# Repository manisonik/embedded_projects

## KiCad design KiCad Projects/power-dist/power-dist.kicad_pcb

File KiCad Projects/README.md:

# embedded_projects
Safe source for KiCad , LTspice, and MicroCap projects.

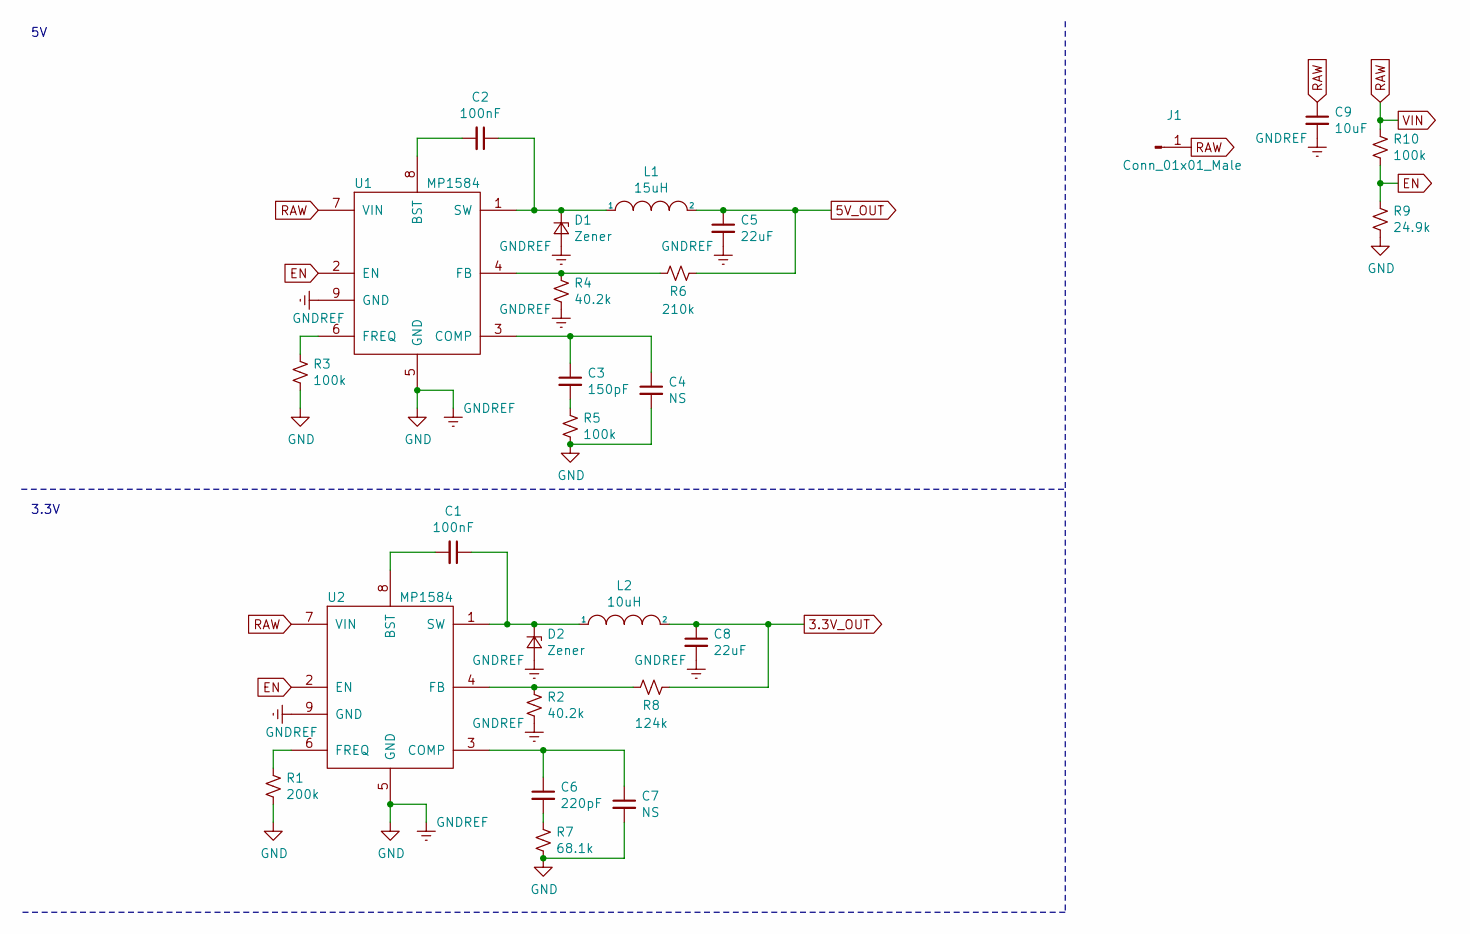
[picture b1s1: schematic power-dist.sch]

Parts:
C1, C2: 100nF; C_0201
C3: 150pF; C_0201
C4, C7: NS; C_0201
C5, C8: 22uF; C_0201
C6: 220pF; C_0201
C9: 10uF; CP_Elec_4x4.5
D1, D2: Zener; D_0603
J1: Conn_01x01_Male; SolderWirePad_4xSquare_0-8mmDrill
L1: 15uH; L_1210
L2: 10uH; L_1210
R1: 200k; R_0201
R2, R4: 40.2k; R_0201
R3, R5, R10: 100k; R_0201
R6: 210k; R_0201
R7: 68.1k; R_0201
R8: 124k; R_0201
R9: 24.9k; R_0201
U1, U2: MP1584; SOIC-8-1EP_3.9x4.9mm_Pitch1.27mm

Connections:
3.3V_OUT: C8.1, L2.2, R8.1
5V_OUT: C5.1, L1.2, R6.1
EN: R9.1, R10.2, U1.2 (EN), U2.2 (EN)
GND: C4.2, C5.2, C7.2, C8.2, C9.2, D1.2 (A), D2.2 (A), R1.2, R2.2, R3.2, R4.2, R5.2, R7.2, R9.2, U1.5 (GND), U1.9 (GND), U2.5 (GND), U2.9 (GND)
unnamed: C1.1, D2.1 (K), L2.1, U2.1 (SW)
unnamed: C1.2, U2.8 (BST)
unnamed: C2.1, D1.1 (K), L1.1, U1.1 (SW)
unnamed: C2.2, U1.8 (BST)
unnamed: C3.1, C4.1, U1.3 (COMP)
unnamed: C3.2, R5.1
unnamed: C6.1, C7.1, U2.3 (COMP)
unnamed: C6.2, R7.1
unnamed: R1.1, U2.6 (FREQ)
unnamed: R2.1, R8.2, U2.4 (FB)
unnamed: R3.1, U1.6 (FREQ)
unnamed: R4.1, R6.2, U1.4 (FB)
RAW: C9.1, J1.1, R10.1, U1.7 (VIN), U2.7 (VIN)

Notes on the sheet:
3.3V

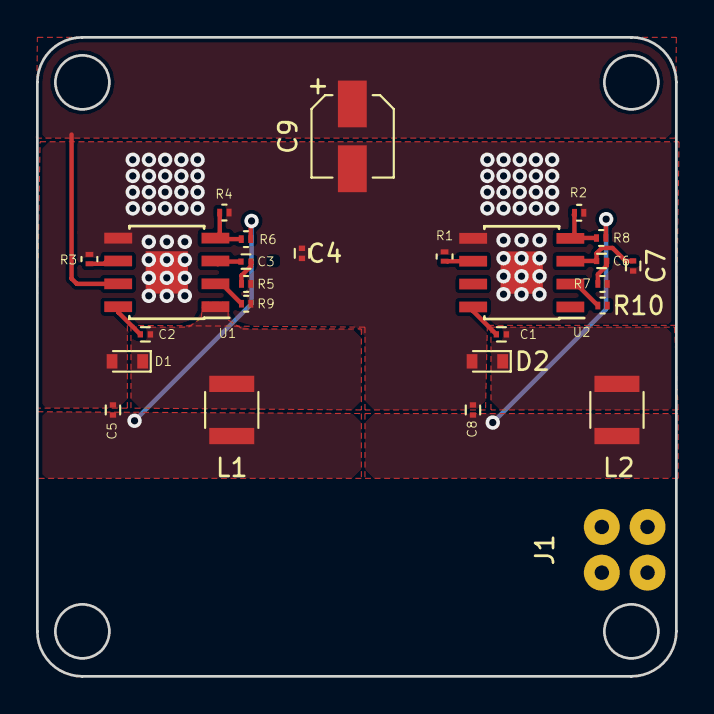
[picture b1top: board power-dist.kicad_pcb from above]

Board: 2 copper layers, 35.5 x 35.5 mm, 26 parts (0 on the bottom side), 17 nets.

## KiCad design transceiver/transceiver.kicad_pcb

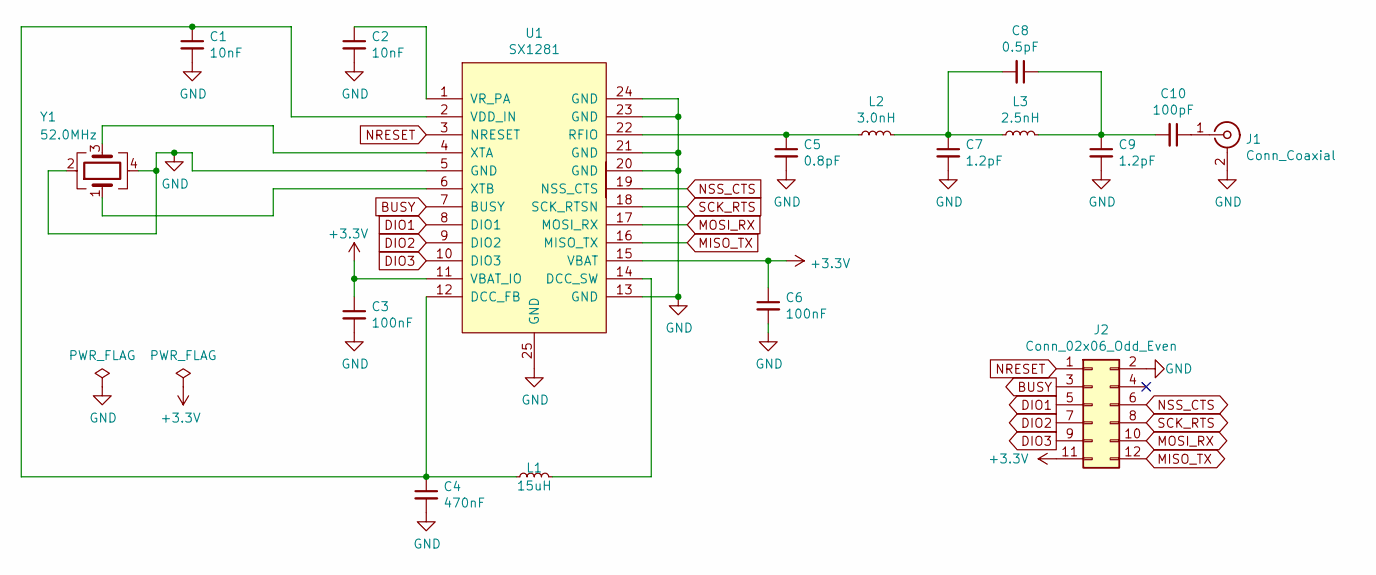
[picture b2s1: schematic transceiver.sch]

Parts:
C1, C2: 10nF; C_0402
C3, C6: 100nF; C_0402
C4: 470nF; C_0402
C5: 0.8pF; C_0402
C7, C9: 1.2pF; C_0402
C8: 0.5pF; C_0402
C10: 100pF; C_0402
J1: Conn_Coaxial; SMA_Amphenol_132289_EdgeMount
J2: Conn_02x06_Odd_Even; Molex_C-Grid_III_90130-1112_2x12_P2.54mm_Vertical
L1: 15uH; L_0805
L2: 3.0nH; L_0402
L3: 2.5nH; L_0402
U1: SX1281; QFN-24-1EP_4x4mm_Pitch0.5mm
Y1: 52.0MHz; Crystal_SMD_2016-4pin_2.0x1.6mm

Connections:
+3V3: C3.1, C6.1, J2.11, U1.11 (VBAT_IO), U1.15 (VBAT)
BUSY: J2.3, U1.7 (BUSY)
DIO1: J2.5, U1.8 (DIO1)
DIO2: J2.7, U1.9 (DIO2)
DIO3: J2.9, U1.10 (DIO3)
GND: C1.2, C2.2, C3.2, C4.2, C5.2, C6.2, C7.2, C9.2, J1.2 (Ext), J2.2, U1.5 (GND), U1.13 (GND), U1.20 (GND), U1.21 (GND), U1.23 (GND), U1.24 (GND), U1.25 (GND), Y1.2, Y1.4
MISO_TX: J2.12, U1.16 (MISO_TX)
MOSI_RX: J2.10, U1.17 (MOSI_RX)
NRESET: J2.1, U1.3 (NRESET)
NSS_CTS: J2.6, U1.19 (NSS_CTS)
unnamed: C1.1, C4.1, L1.1, U1.2 (VDD_IN), U1.12 (DCC_FB)
unnamed: C2.1, U1.1 (VR_PA)
unnamed: C5.1, L2.1, U1.22 (RFIO)
unnamed: C7.1, C8.2, L2.2, L3.1
unnamed: C10.1, J1.1 (In)
unnamed: C8.1, C9.1, C10.2, L3.2
unnamed: L1.2, U1.14 (DCC_SW)
unnamed: U1.4 (XTA), Y1.3
unnamed: U1.6 (XTB), Y1.1
SCK_RTS: J2.8, U1.18 (SCK_RTSN)

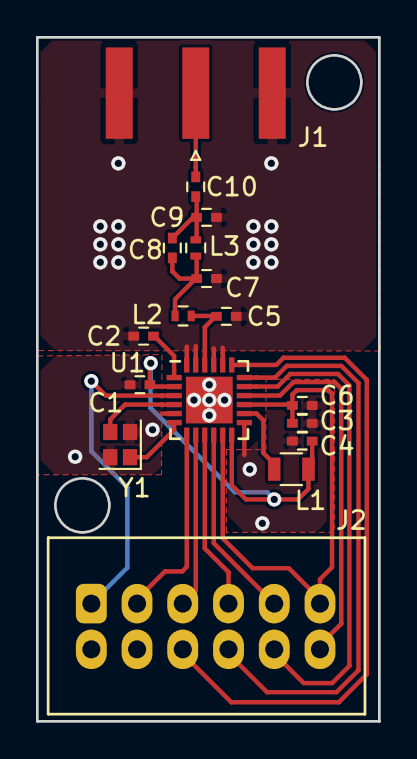
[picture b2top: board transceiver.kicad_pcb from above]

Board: 2 copper layers, 19.0 x 38.0 mm, 17 parts (0 on the bottom side), 20 nets.

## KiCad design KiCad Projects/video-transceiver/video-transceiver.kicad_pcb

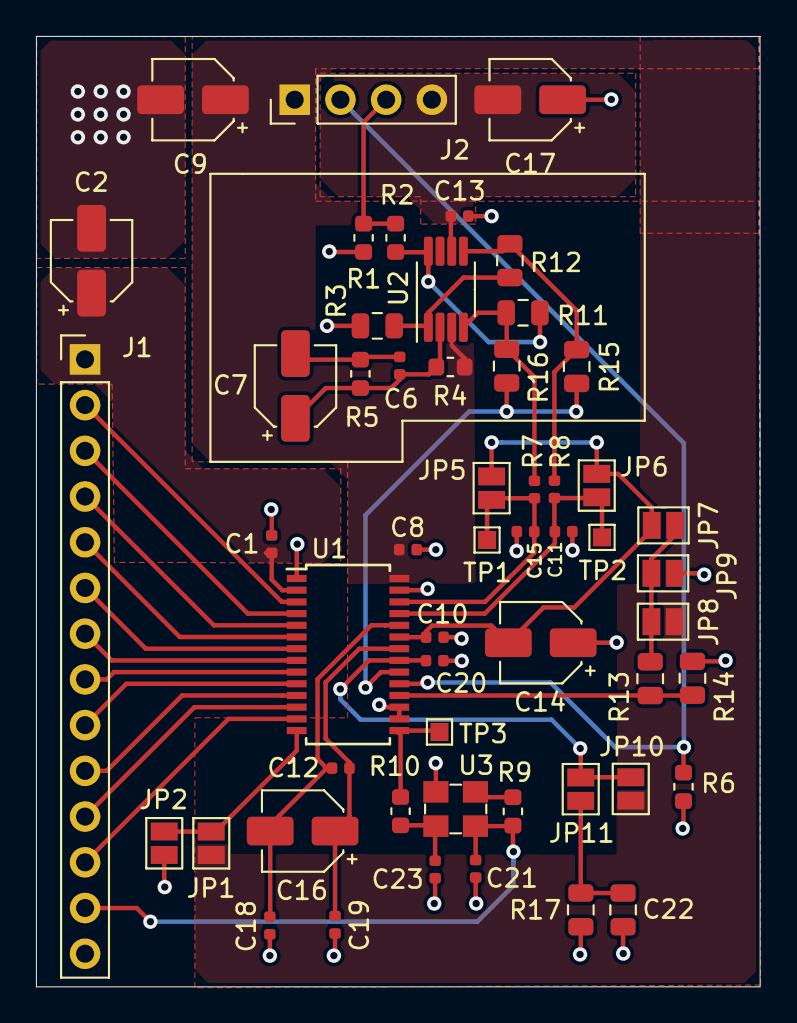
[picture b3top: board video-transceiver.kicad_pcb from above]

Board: 2 copper layers, 40.2 x 52.8 mm, 54 parts (0 on the bottom side), 38 nets.

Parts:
C1, C6, C8, C10, C12, C13, C18, C19, C20, C21: 0.1uF; C_0402_1005Metric
C2, C7, C9, C14, C16, C17: 10uF; CP_Elec_4x5.4
C11, C15: 20pF; C_0402_1005Metric
C22: 1uF; C_0805_2012Metric
C23: 15pF; C_0402_1005Metric
J1: Conn_01x14_Male; PinHeader_1x14_P2.54mm_Vertical
J2: Conn_01x04_Male; PinHeader_1x04_P2.54mm_Vertical
JP1, JP2, JP5, JP6, JP7, JP8, JP9, JP10, JP11: Jumper; SolderJumper-2_P1.3mm_Open_Pad1.0x1.5mm
R1, R6, R10: 50R; R_0603_1608Metric
R2: 1R; R_0603_1608Metric
R3: 25R; R_0805_2012Metric
R4, R5, R9: 1k; R_0603_1608Metric
R7, R8: 10R; R_0402_1005Metric
R11, R12, R13, R14, R15, R16, R17: TBD; R_0805_2012Metric
TP1, TP2, TP3: TestPoint; TestPoint_Pad_1.0x1.0mm
U1: AD9203; TSSOP-28_4.4x9.7mm_P0.65mm
U2: AD8138; MSOP-8_3x3mm_P0.65mm
U3: SIT8208AI-2F-33E-27.000000Y; Oscillator_SMD_SiT8208-4Pin_3.2x2.5mm_P0.75mm

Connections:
A: R8.1, R12.1, R15.2, U2.5
AVDD: C8.2, C9.1, J2.1, JP1.2, JP8.1, JP10.2, R4.2, U1.28, U2.3
AVSS: C13.1, C17.2, J2.4, U2.6
B: R7.1, R11.1, R16.2, U2.4
CLAMP: J2.2, R6.2, U1.19
CLK: R10.1, TP3.1, U1.15
D0: J1.2, U1.3
D1: J1.3, U1.4
D2: J1.4, U1.5
D3: J1.5, U1.6
D4: J1.6, U1.7
D5: J1.7, U1.8
D6: J1.8, U1.9
D7: J1.9, U1.10
D8: J1.10, U1.11
D9: J1.11, U1.12
DRVDD: C1.2, C2.1, J1.1, U1.2
GND: C1.1, C2.2, C8.1, C9.2, C10.2, C11.1, C13.2, C14.1, C15.1, C17.1, C18.1, C19.1, C20.1, C21.2, C22.2, C23.2, J1.14, JP2.2, JP9.1, R1.1, R3.2, R6.1, R14.1, R17.2, U1.1, U1.16, U1.17, U1.27, U3.2
unnamed: C6.1, C7.1, R4.1, R5.2, U2.2
unnamed: C6.2, C7.2, R5.1
unnamed: C10.1, C14.2, JP5.2, JP6.2, JP7.2, U1.23
unnamed: C11.2, JP6.1, R8.2, TP2.1, U1.25
unnamed: C12.1, C16.2, C18.2, U1.24
unnamed: C12.2, C16.1, C19.2, U1.22
unnamed: C15.2, JP5.1, R7.2, TP1.1, U1.26
unnamed: C22.1, JP11.2, R17.1
unnamed: C23.1, R10.2, U3.3
unnamed: JP1.1, JP2.1, U1.14
unnamed: JP7.1, JP8.2, JP9.2, R13.2
unnamed: R9.1, U3.1
unnamed: R2.1, R11.2, U2.8
unnamed: R3.1, R12.2, U2.1
unnamed: R15.1, R16.1, U1.20
OTR: J1.12, U1.13
PWRCON: C20.2, JP10.1, JP11.1, U1.21
REFSENSE: R13.1, R14.2, U1.18
VDD: C21.1, J1.13, R9.2, U3.4
VID: J2.3, R1.2, R2.2

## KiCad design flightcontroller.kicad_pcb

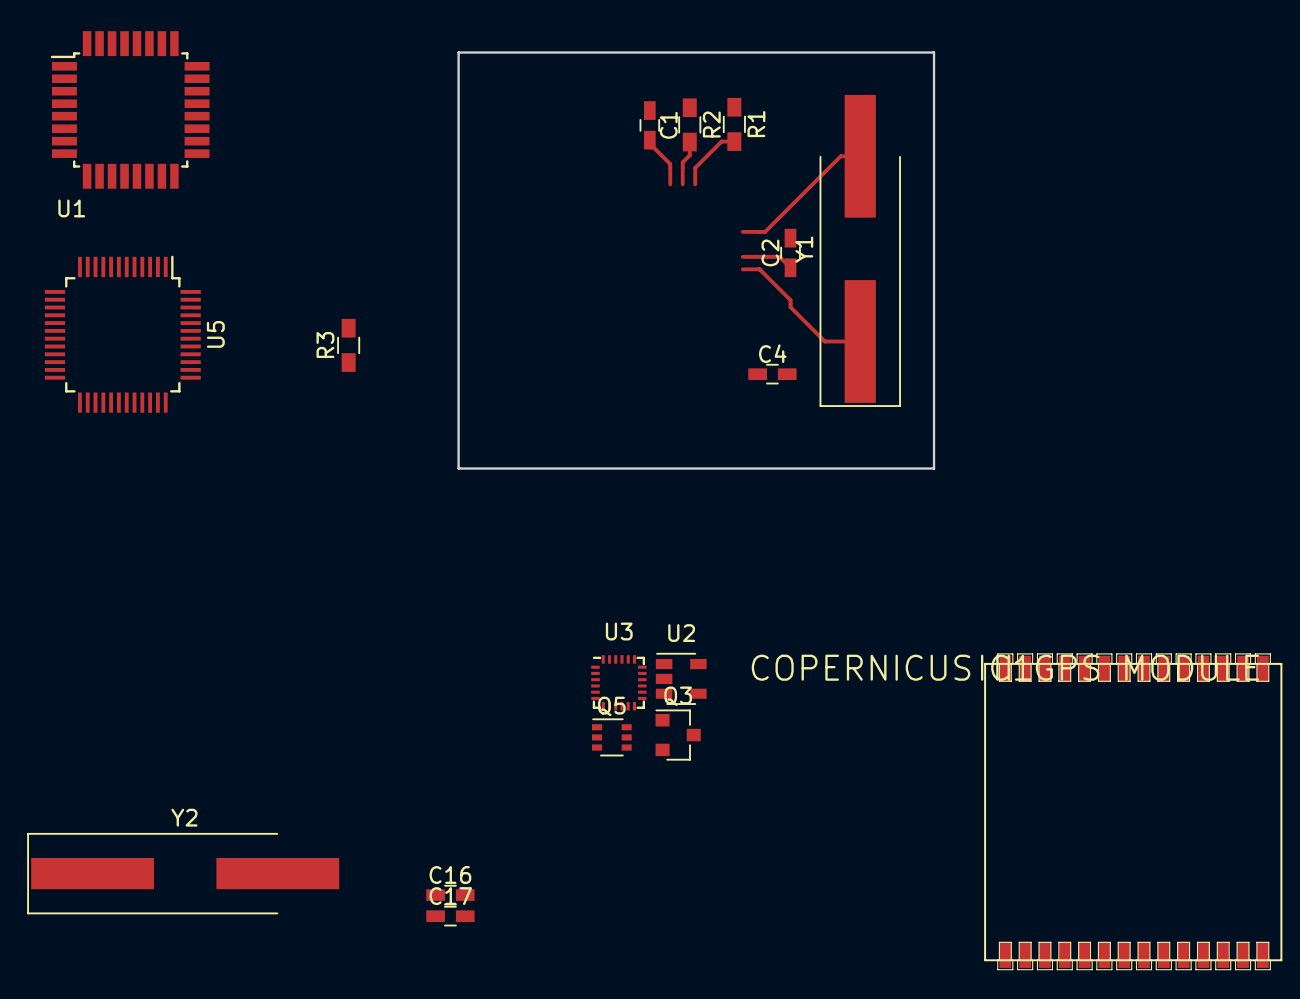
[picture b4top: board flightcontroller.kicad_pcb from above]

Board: 2 copper layers, 30.5 x 26.7 mm, 17 parts (0 on the bottom side), 15 nets.

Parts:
C1, C4: 0.1uF; C_0603_HandSoldering
C2: 10uF; C_0603_HandSoldering
C16, C17: 10pF; C_0603_HandSoldering
IC1: COPERNICUS II GPS MODULE; COPERNICUS
Q3: CMPT404A; SOT-23
Q5: FDG6316P; SOT-363_SC-70-6
R1: 1k; R_0603_HandSoldering
R2: 100k; R_0603_HandSoldering
R3: 10K; R_0603_HandSoldering
U1: BMP180; TQFP-32_7x7mm_Pitch0.8mm
U2: MIC5219-3.3BM5; SOT-23-5
U3: MPU-9250; QFN-24_3x3mm_Pitch0.4mm
U5: STM32F103CBTx; LQFP-48_7x7mm_Pitch0.5mm
Y1: 8; Crystal_SMD_HC49-SD_HandSoldering
Y2: 8MHz; Crystal_SMD_HC49-SD_HandSoldering

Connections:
GND: C1.2, C2.2, C4.2, C16.2, C17.2, IC1.1, IC1.2, IC1.4, IC1.13, IC1.14, IC1.15, IC1.27, IC1.28, R3.2, U1.7, U2.2, U3.18, U5.8, U5.23, U5.35, U5.47
unnamed: C4.1, U3.10
unnamed: U5.5, Y1.1
unnamed: U5.6, Y1.2
unnamed: Q3.1, R1.1
unnamed: IC1.5, Q5.2, R2.2
unnamed: Q3.2, Q5.1
OSCA: C16.1, Y2.1
OSCB: C17.1, Y2.2
RAW: C2.1, U2.1, U2.3
RXDB: IC1.20, U5.31
SCL: U3.23, U5.42
SDA: U1.6, U3.24, U5.43
TXDA: IC1.23, U5.30
VCC: C1.1, IC1.6, IC1.12, Q5.3, R2.1, U1.2, U1.3, U2.5, U3.8, U3.13, U5.9, U5.24, U5.36, U5.48

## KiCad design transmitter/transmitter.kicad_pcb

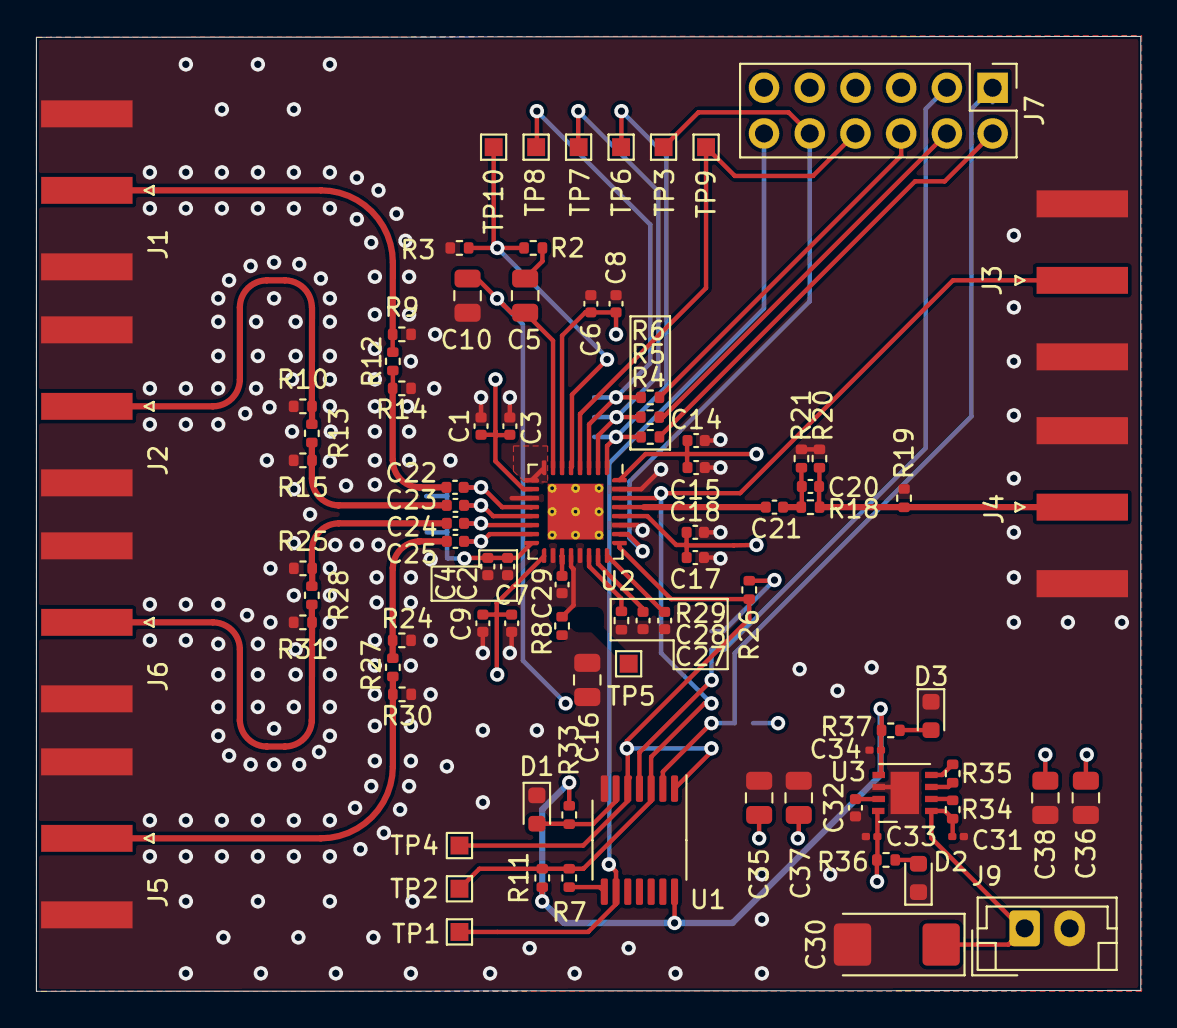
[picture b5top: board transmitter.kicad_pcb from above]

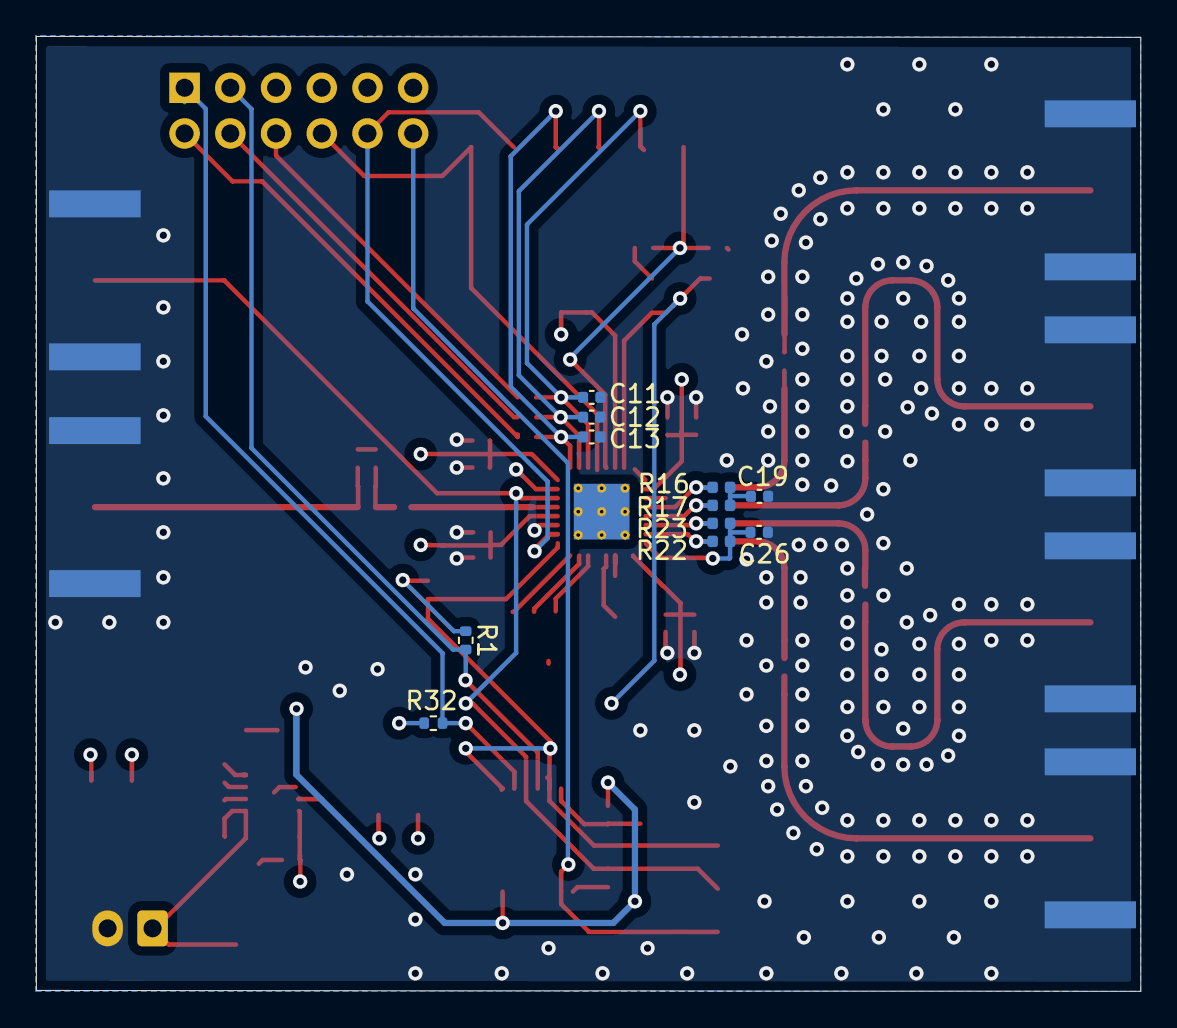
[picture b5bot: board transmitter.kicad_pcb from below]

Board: 4 copper layers, 61.3 x 53.0 mm, 99 parts (11 on the bottom side), 48 nets.

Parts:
C1, C2, C6, C7, C14, C17, C22, C23, C24, C25: 100pF; C_0402_1005Metric
C3, C4, C8, C9, C15, C18, C19, C21, C26, C32: 0.01uF; C_0402_1005Metric
C5, C37, C38: 0.1uF; C_0805_2012Metric
C10: 0.012uF; C_0805_2012Metric
C11, C12, C13: 10pF; C_0402_1005Metric
C16: 820pF; C_0805_2012Metric
C20: open; C_0402_1005Metric
C27, C28, C29: 1.0uF; C_0402_1005Metric
C30: 10uF; CP_EIA-6032-20_AVX-F
C31, C33, C34: 2.2uF; C_0201_0603Metric
C35, C36: 4.7uF; C_0805_2012Metric
D1, D2, D3: LED; D_0603_1608Metric
J1: RFOUTAP; SMA_Amphenol_132289_EdgeMount
J2: RFOUTAN; SMA_Amphenol_132289_EdgeMount
J3: MUXOUT; SMA_Amphenol_132289_EdgeMount
J4: REFIN; SMA_Amphenol_132289_EdgeMount
J5: RFOUTBN; SMA_Amphenol_132289_EdgeMount
J6: RFOUTBP; SMA_Amphenol_132289_EdgeMount
J7: Conn_02x06_Odd_Even; PinHeader_2x06_P2.54mm_Vertical
J9: Conn_01x02_Female; JST_EH_B2B-EH-A_1x02_P2.50mm_Vertical
R1, R32, R33: 5.1K; R_0402_1005Metric
R2: 30.1R; R_0402_1005Metric
R3: 90.9R; R_0402_1005Metric
R4, R5, R6: 120R; R_0402_1005Metric
R7, R11, R19, R20, R21, R26: open; R_0402_1005Metric
R8: 240R; R_0402_1005Metric
R9, R10, R14, R15, R24, R25, R30, R31: 300R; R_0402_1005Metric
R12, R13, R27, R28: 18R; R_0402_1005Metric
R16, R17, R22, R23: 27nH; L_0402_1005Metric
R18: 0R; R_0402_1005Metric
R29, R36, R37: 5.1k; R_0402_1005Metric
R34, R35: 10k; R_0402_1005Metric
TP1: TestPoint; TestPoint_Pad_1.0x1.0mm
TP2: MUX_OUT; TestPoint_Pad_1.0x1.0mm
TP3: RF_EN; TestPoint_Pad_1.0x1.0mm
TP4: LD; TestPoint_Pad_1.0x1.0mm
TP5: VTUNE; TestPoint_Pad_1.0x1.0mm
TP6: CLK; TestPoint_Pad_1.0x1.0mm
TP7: DATA; TestPoint_Pad_1.0x1.0mm
TP8: LE; TestPoint_Pad_1.0x1.0mm
TP9: CE; TestPoint_Pad_1.0x1.0mm
TP10: SW; TestPoint_Pad_1.0x1.0mm
U1: SN74LV07ADR; TSSOP-14_4.4x5mm_P0.65mm
U2: MAX2870; TQFN-32-1EP_5x5mm_P0.5mm_EP3.1x3.1mm_ThermalVias
U3: MAX8559ETAAA; TDFN-8-1EP_3x3mm_P0.65mm_EP1.5x2.3mm

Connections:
+5V: C30.1, C31.1, J9.1, R34.2, R35.2, U3.1, U3.4
GND: C1.1, C2.1, C3.1, C4.1, C6.1, C7.1, C8.1, C9.1, C10.1, C11.2, C12.2, C13.1, C14.2, C15.2, C16.1, C17.2, C18.2, C19.2, C26.2, C27.1, C28.1, C29.1, C30.2, C31.2, C32.1, C33.2, C34.2, C35.2, C36.2, C37.2, C38.2, D1.1, D2.1, D3.1, J1.2, J2.2, J3.2, J4.2, J5.2, J6.2, J9.2, R3.2, R9.1, R10.1, R14.1, R15.1, R19.1, R20.1, R21.1, R24.1, R25.1, R29.1, R30.1, R31.1, U1.7, U2.8, U2.9, U2.11, U2.18, U2.21, U2.27, U2.31, U3.6, U3.9
LD: J7.1, R32.2, U1.2
MAX2870_CE: J7.8, TP9.1, U2.4
MAX2870_CLK: J7.2, R4.2
MAX2870_DATA: J7.4, R5.2
MAX2870_LE: J7.6, R6.2
MAX2870_MUX: J7.3, R1.2, U1.4
unnamed: C5.1, R2.1
unnamed: C5.2, C10.2, R8.2, U2.7
unnamed: C11.1, R6.1, TP8.1, U2.3
unnamed: C12.1, R5.1, TP7.1, U2.2
unnamed: C13.2, R4.1, TP6.1, U2.1
unnamed: C16.2, R8.1, TP5.1, U2.20
unnamed: C19.1, R16.2, R17.2
unnamed: C20.1, J4.1, R18.1, R19.2, R20.2
unnamed: C20.2, C21.2, R18.2, R21.2
unnamed: C21.1, U2.29
unnamed: C22.1, R12.1, R14.2
unnamed: C22.2, R16.1, U2.12
unnamed: C23.1, R13.1, R15.2
unnamed: C23.2, R17.1, U2.13
unnamed: C24.1, R25.2, R28.2
unnamed: C24.2, R23.2, U2.14
unnamed: C25.1, R24.2, R27.2
unnamed: C25.2, R22.2, U2.15
unnamed: C27.2, U2.24
unnamed: C28.2, U2.23
unnamed: C29.2, U2.19
unnamed: C32.2, U3.7
unnamed: D1.2, R33.2, U1.6
unnamed: D2.2, R36.2
unnamed: D3.2, R37.2
unnamed: J1.1, R9.2, R12.2
unnamed: J2.1, R10.2, R13.2
unnamed: J3.1, R7.1, R11.2, TP2.1, U1.3, U2.30
unnamed: J5.1, R27.1, R30.2
unnamed: J6.1, R28.1, R31.2
unnamed: R2.2, R3.1, TP10.1, U2.5
unnamed: R7.2, U1.8
unnamed: R26.2, TP4.1, U1.1, U1.5, U2.25
unnamed: R29.2, U2.22
unnamed: R34.1, U3.2
unnamed: R35.1, U3.3
PHASE_ADJ: J7.12, TP1.1, U1.9
RF_EN: J7.10, TP3.1, U2.26
VCC_PLL: C1.2, C3.2, C6.2, C8.2, C14.1, C15.1, C17.1, C18.1, C34.1, C36.1, C38.1, R1.1, R11.1, R26.1, R32.1, R33.1, R37.1, U1.14, U2.6, U2.10, U2.28, U2.32, U3.5
VCC_VCO: C2.2, C4.2, C7.2, C9.2, C26.1, C33.1, C35.1, C37.1, R22.1, R23.1, R36.1, U2.16, U2.17, U3.8
